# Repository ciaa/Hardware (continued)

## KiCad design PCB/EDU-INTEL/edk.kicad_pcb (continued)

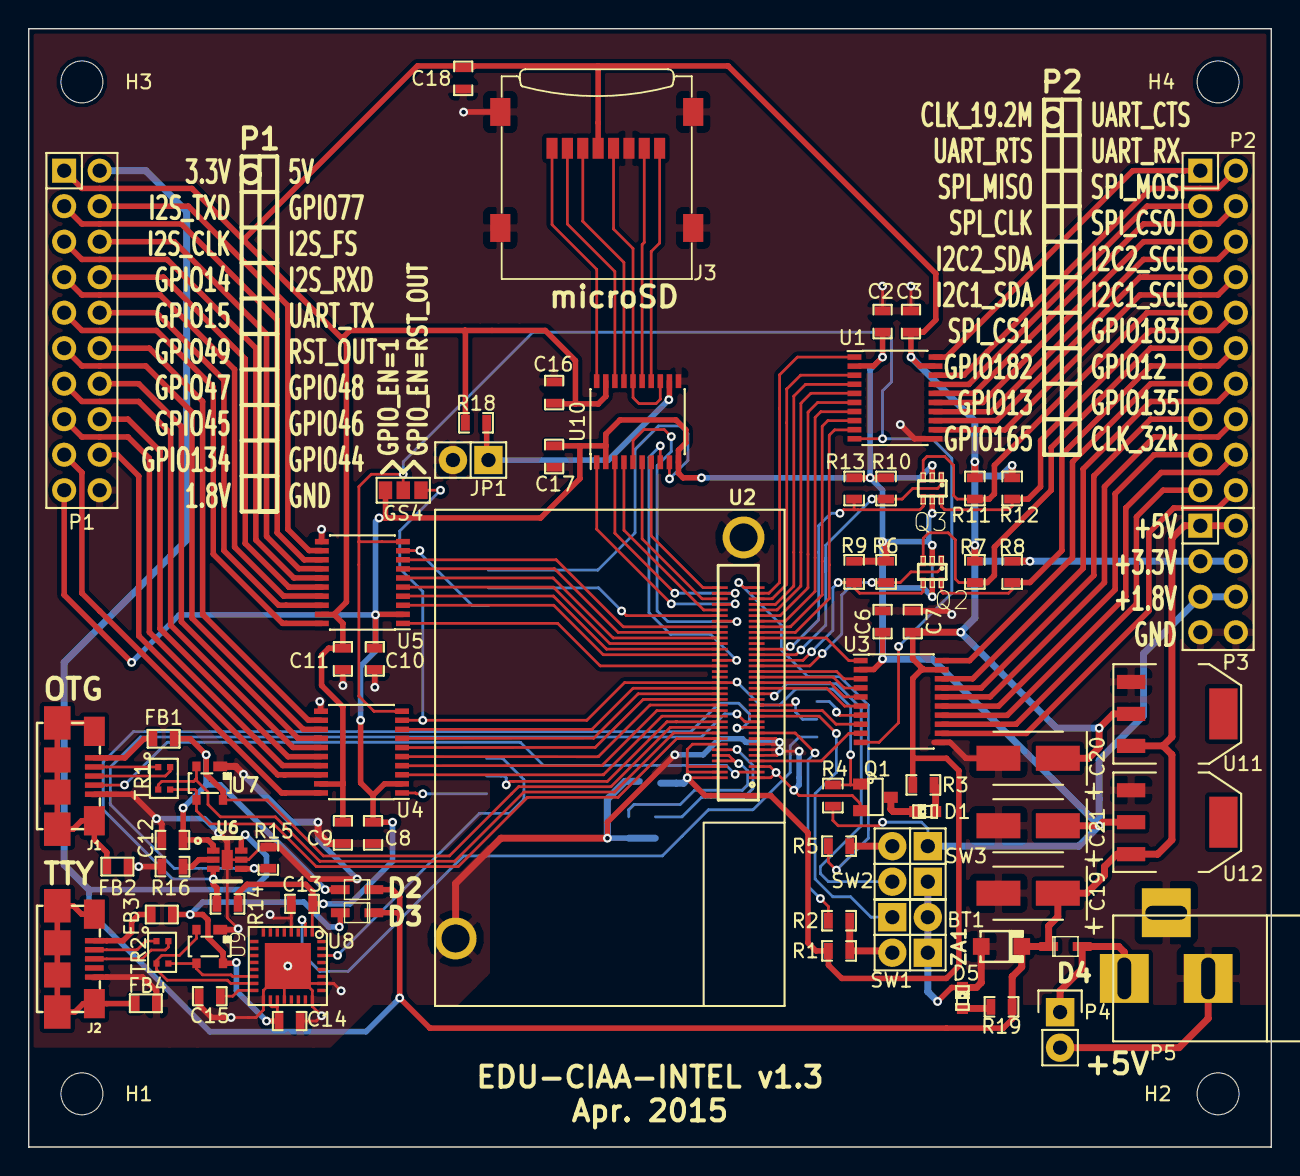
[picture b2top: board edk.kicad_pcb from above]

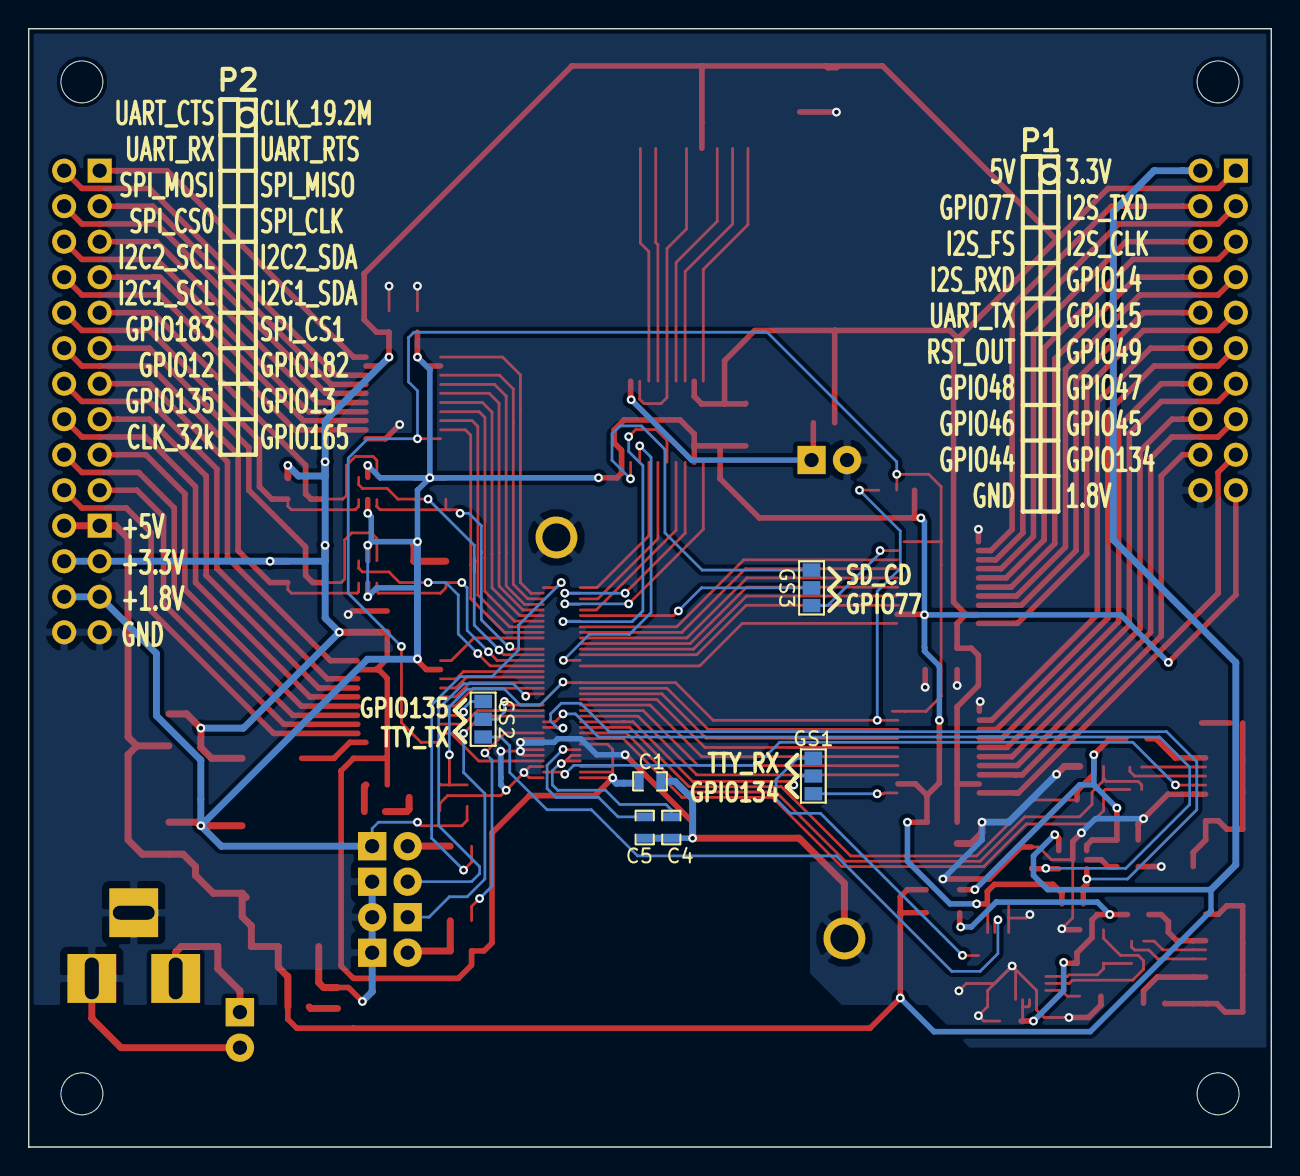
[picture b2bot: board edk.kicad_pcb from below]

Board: 2 copper layers, 88.9 x 80.0 mm, 87 parts (6 on the bottom side), 128 nets.

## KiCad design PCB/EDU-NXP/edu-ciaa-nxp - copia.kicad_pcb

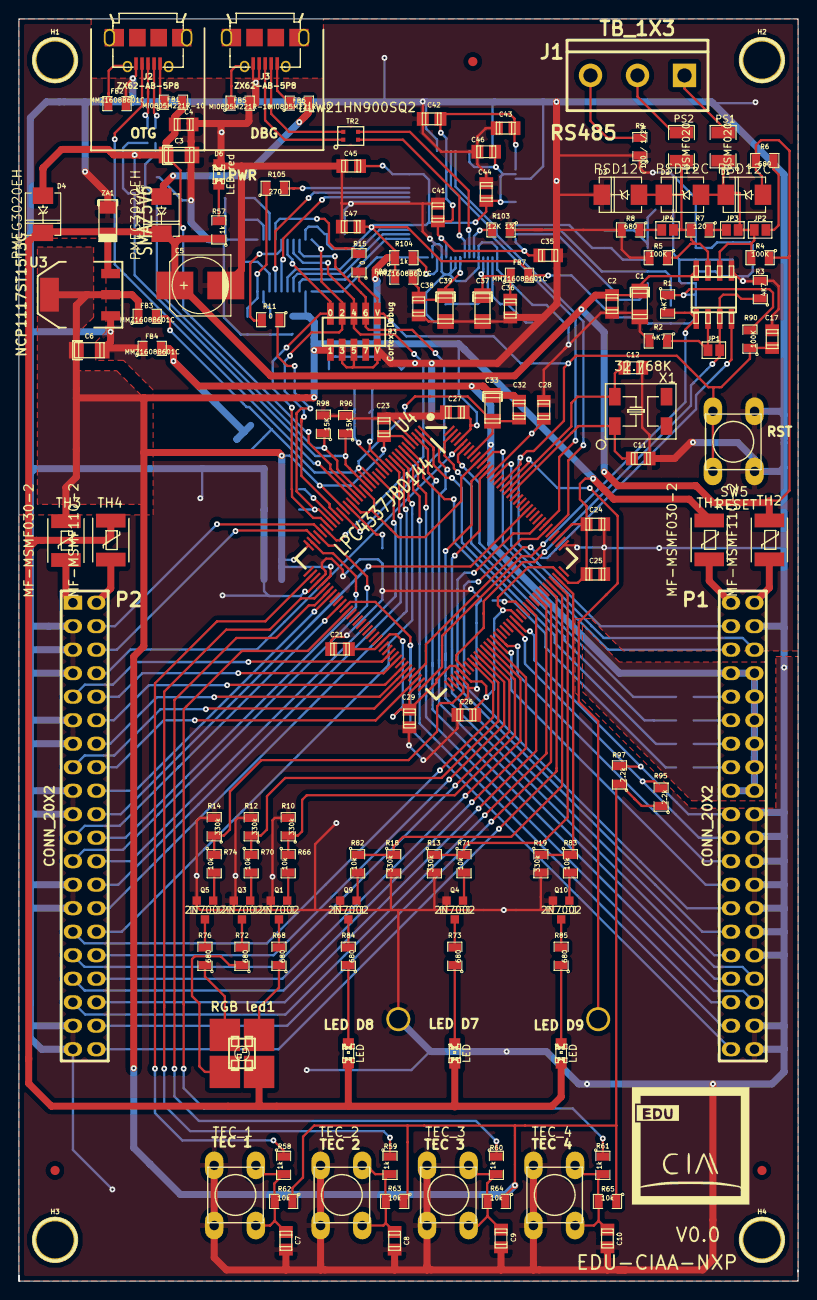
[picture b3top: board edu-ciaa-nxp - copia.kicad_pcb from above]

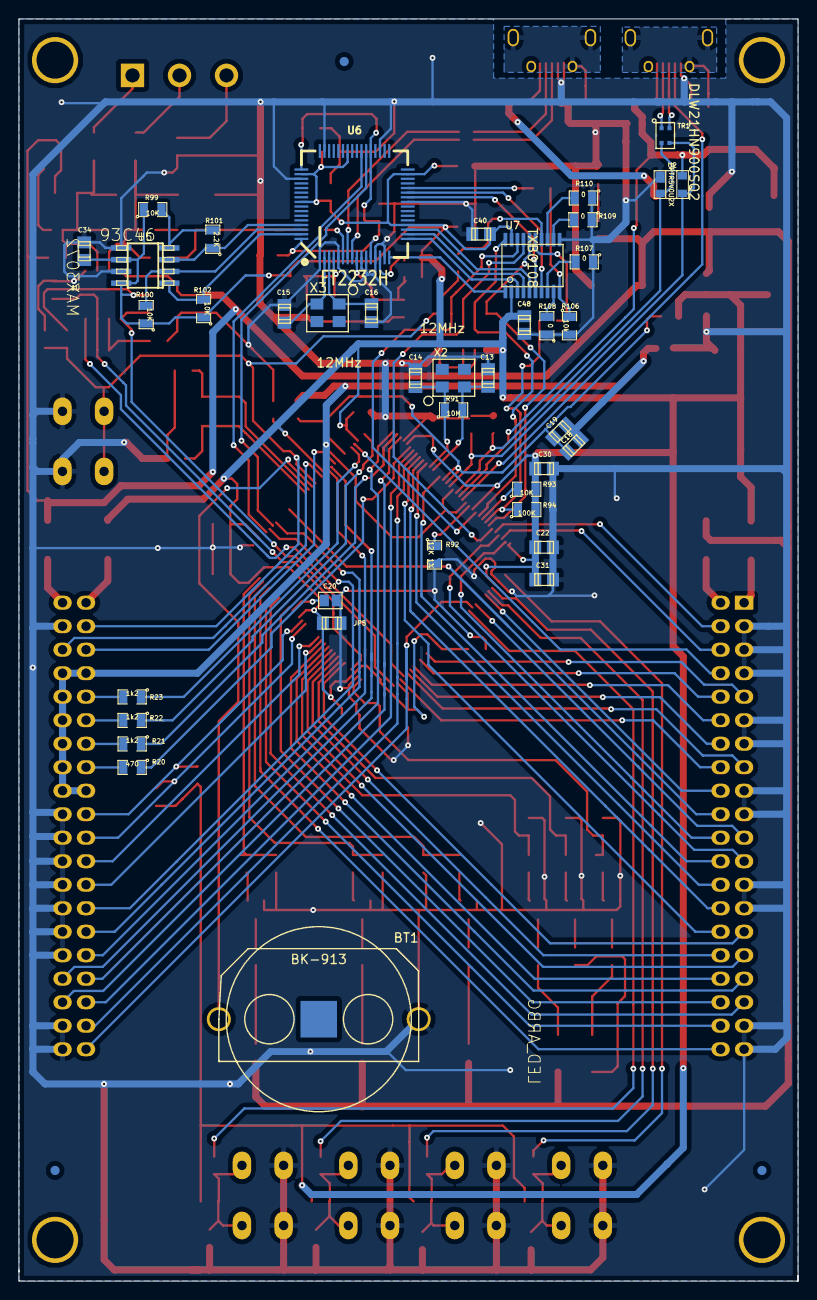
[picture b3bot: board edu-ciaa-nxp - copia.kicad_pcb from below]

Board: 2 copper layers, 84.2 x 136.4 mm, 181 parts (39 on the bottom side), 160 nets.

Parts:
BT1: BK-913; BK-913-ND
C1: 10uF / 6V3; c_1206_tantalio
C2, C4, C7, C8, C9, C10, C17, C18, C19, C20, C21, C22, C23, C24, C25, C26, C27, C28, C29, C30, C31, C32, C34, C36, C38, C40, C41, C42, C43, C44, C45, C46, C47, C48: 100nF; c_0805
C3, C6, C33, C37, C39: 10uF; c_1206_tantalio_1
C5: 330uF; c_elec_6.3x7.7
C11, C12: 15p; c_0805
C13, C14: 20p; c_0805
C15, C16: 22p; c_0805
C35: 3.3uF; c_0805
D1, D2, D3: PSD12C; DO-214AA(SMB)
D4, D5: PMEG3020EH; DO-214AA(SMB)
D6: LED red; LED-0805
D7, D8, D9: LED; LED-0805
F1, F2, F3: fiducial; Fiducial_1mm_TOP
F4, F5, F6: fiducial; Fiducial_1mm_BOT
FB1, FB5, FB6: MI0805M221R-10; SM0805
FB2, FB3, FB4, FB7, FB8: MMZ1608B601C; SM0805
H1, H2, H3, H4: 4mm; 1pin
J1: TB_1X3; bornier3
J2, J3: ZX62-AB-5P8; USB_microAB_ZX62-AB-5P8
JP1, JP2, JP3, JP4: JUMPER-2; GS2
JP5: ISP; GS2
LED1: LED_ARBG; PLCC-4
P1, P2: CONN_20X2; PIN_ARRAY_20X2
P3: Cortex-Debug; Pin_Array_5x2_1.27mm_SMD
PS1, PS2: USMF020; SM1210
Q1, Q3, Q4, Q5, Q9, Q10: 2N7002; SOT23GDS
R1, R2, R3: 4K7; SM0805
R4, R5, R90, R94: 100K; SM0805
R6, R8, R68, R72, R73, R76, R84, R85: 680; SM0805
R7: 120; SM0805
R9: 100 / 1/2W; SM0805
R10, R12, R13, R14, R18, R19: 330k; SM0805
R11, R15, R107, R108, R109, R110: 0; SM0805
R20: 470; SM0805
R21, R22, R23: 1k2; SM0805
R57, R58, R59, R60, R61, R104: 1k; SM0805
R62, R63, R64, R65, R66, R70, R71, R74, R82, R83, R106: 10k; SM0805
R91: 10M; SM0805
R92, R103: 12K 1%; SM0805
R93, R99, R100, R102: 10K; SM0805
R95, R97: 2.2k; SM0805
R96, R98: 15K; SM0805
R101: 2.2K; SM0805
R105: 270; SM0805
SW1: TEC_1; PUSH_SWITCH_THT
SW2: TEC_2; PUSH_SWITCH_THT
SW3: TEC_3; PUSH_SWITCH_THT
SW4: TEC_4; PUSH_SWITCH_THT
SW5: RESET; PUSH_SWITCH_THT
TH1, TH3: MF-MSMF030-2; MF-MSMF
TH2, TH4: MF-MSMF110-2; MF-MSMF
TR1, TR2: DLW21HN900SQ2; SRF2012
U1: MAX3072; -SOIC8
U2: PRTR5V0U2X; sot143B
U3: NCP1117ST15T3G; SOT223
U4: LPC4337JBD144; LQFP144-M05
U5: 93C46; -SOIC8
U6: FT2232H; LQFP64-M05
U7: TXB0108; tssop-20
X1: 32.768K; 4SOJ
X2, X3: 12MHz; FA238V-XTAL
ZA1: SMAZ5V6; SOD123F

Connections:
+3.3V: C6.1, C20.2, C21.2, C22.2, C23.2, C24.2, C25.2, C26.2, C27.2, C28.2, C29.2, C30.2, C31.2, C34.1, C40.2, C44.1, C45.1, C46.1, C47.1, C48.2, FB3.1, FB7.2, FB8.2, P3.1, R1.1, R62.1, R63.1, R64.1, R65.1, R90.2, R93.2, R94.2, R95.1, R97.1, R99.1, R100.1, R102.1, R104.1, TH1.2, TH3.2, U3.2, U3.4, U4.5, U4.25, U4.36, U4.41, U4.59, U4.71, U4.77, U4.94, U4.107, U4.111, U4.131, U4.141, U5.6, U5.8, U6.20, U6.31, U6.42, U6.50, U6.56, U7.2, U7.19
+3.3VADC: C18.1, C19.1, C32.1, C33.2, FB3.2, U4.16, U4.17, U4.137
+5V: C1.2, C2.1, C5.1, D1.1, D4.2, D5.2, D7.1, D8.1, D9.1, LED1.4, R4.1, R6.1, R57.1, TH2.2, TH4.2, U1.8, U3.3, ZA1.1
/CPU/ADC0_1: R21.1, U4.2
/CPU/ADC0_2: R22.1, U4.143
/CPU/ADC0_3: R23.1, U4.139
/CPU/CAN_RD: P1.27, U4.114
/CPU/CAN_TD: P1.29, U4.116
/CPU/CHJ3: FB5.1, J3.7
/CPU/DAC: R20.1, U4.6
/CPU/EECLK: R100.2, U5.2, U6.62
/CPU/EECS: R102.2, U5.1, U6.63
/CPU/EEDATA: R101.1, U5.3, U6.61
/CPU/ENET_CRS_DV: P2.10, U4.64
/CPU/ENET_MDC: P2.8, U4.140
/CPU/ENET_MDIO: P2.12, U4.66
/CPU/ENET_REF_CLK: P2.15, U4.68
/CPU/ENET_RXD0: P2.9, U4.62
/CPU/ENET_RXD1: P2.4, U4.32
/CPU/ENET_TXD0: P2.14, U4.67
/CPU/ENET_TXD1: P2.16, U4.70
/CPU/ENET_TX_EN: P2.6, U4.34
/CPU/FT_OE: R105.2, U6.28
/CPU/FT_RST: U6.27, U7.7
/CPU/FT_TCK: U6.16, U7.1
/CPU/FT_TDI: U6.17, U7.3
/CPU/FT_TDO: U6.18, U7.4
/CPU/FT_TMS: U6.19, U7.5
/CPU/FT_TRST: U6.26, U7.6
/CPU/FT_XTIN: C15.2, U6.2, X3.2
/CPU/FT_XTOUT: C16.2, U6.3, X3.1
/CPU/GPIO0: P2.29, U4.80
/CPU/GPIO1: P2.32, U4.82
/CPU/GPIO2: P2.31, U4.83
/CPU/GPIO3: P2.34, U4.85
/CPU/GPIO4: P2.33, U4.86
/CPU/GPIO5: P2.36, U4.97
/CPU/GPIO6: P2.35, U4.100
/CPU/GPIO7: P2.38, U4.101
/CPU/GPIO8: P2.40, U4.103
/CPU/I2C_SCL: P1.21, R95.2, U4.92
/CPU/I2C_SDA: P1.19, R97.2, U4.93
/CPU/ISP: P1.5, U4.134
/CPU/LCD1: P2.30, U4.9
/CPU/LCD2: P2.28, U4.10
/CPU/LCD3: P2.26, U4.11
/CPU/LCD4: P2.22, U4.35
/CPU/LCD_RS: P2.24, U4.15
/CPU/LED0_B: R10.1, R66.1, U4.84
/CPU/LED0_G: R12.1, R70.1, U4.81
/CPU/LED0_R: R14.1, R74.1, U4.75
/CPU/LED1: R18.1, R82.1, U4.104
/CPU/LED2: R13.1, R71.1, U4.105
/CPU/LED3: R19.1, R83.1, U4.106
/CPU/PULS_0: R58.1, U4.38
/CPU/PULS_1: R59.1, U4.42
/CPU/PULS_2: R60.1, U4.43
/CPU/PULS_3: R61.1, U4.49
/CPU/RESET: C17.1, P1.3, P3.10, R15.1, R90.1, SW5.1, SW5.2, U4.128
/CPU/RS232_RXD: P1.23, U4.88
/CPU/RS232_TXD: P1.25, U4.87
/CPU/RS485_DIR: JP1.1, R3.1, U1.3, U4.78
/CPU/RS485_RXD: R1.2, U1.1, U4.72
/CPU/RS485_TXD: U1.4, U4.69
/CPU/RST: R15.2, U7.14
/CPU/RTCX1: C11.2, U4.125, X1.1
/CPU/RTCX2: C12.2, U4.126, X1.4
/CPU/SPI_MISO: P2.18, U4.44
/CPU/SPI_MOSI: P2.21, U4.47
/CPU/SPI_SCK: P2.20, U4.120
/CPU/TCK: P3.4, U4.27, U7.20
/CPU/TDI: P3.8, U4.26, U7.18
/CPU/TDO: P3.6, U4.31, U7.17
/CPU/TEC_COL0: P1.39, U4.48
/CPU/TEC_COL1: P1.31, U4.132
/CPU/TEC_COL2: P1.34, U4.133
/CPU/TEC_F0: P1.33, U4.1
/CPU/TEC_F1: P1.36, U4.3
/CPU/TEC_F2: P1.37, U4.8
/CPU/TEC_F3: P1.35, U4.7
/CPU/TMS: P3.2, U4.30, U7.16
/CPU/TRST: R11.2, U7.15
/CPU/U2_RXD: U4.115, U6.38
/CPU/U2_TXD: U4.113, U6.39
/CPU/USB_DEBUG_VBUS: D5.1, FB6.2
/CPU/USB_DM: R98.1, TR1.2, U2.2, U4.20
/CPU/USB_DP: R96.1, TR1.3, U2.3, U4.18
/CPU/USB_ID: J2.4, U4.22
/CPU/USB_JTAG_1.8V: C35.1, C41.1, C42.1, C43.1, U6.12, U6.37, U6.49, U6.64
/CPU/USB_JTAG_DM: TR2.3, U6.7
/CPU/USB_JTAG_DP: TR2.2, U6.8
/CPU/USB_VBUS: C3.1, C4.1, D4.1, FB1.2, U2.4, U4.21
/CPU/XTAL1: C14.2, R91.1, U4.12, X2.1
/CPU/XTAL2: C13.2, R91.2, U4.13, X2.2
/CPU/nTRST: R11.1, R94.1, U4.29
/GPIO/LCD_EN: P2.23, U4.33
/GPIO/WAKEUP: P1.6, U4.130
/USB OTG/CHJ2: FB2.2, J2.7
GND: BT1.2, C1.1, C2.2, C3.2, C4.2, C5.2, C6.2, C7.2, C8.2, C9.2, C10.2, C11.1, C12.1, C13.1, C14.1, C15.1, C16.1, C17.2, C20.1, C21.1, C22.1, C23.1, C24.1, C25.1, C26.1, C27.1, C28.1, C29.1, C30.1, C31.1, C34.2, C35.2, C36.2, C37.2, C38.2, C39.2, C40.1, C41.2, C42.2, C43.2, C44.2, C45.2, C46.2, C47.2, C48.1, D3.2, D6.2, FB2.1, FB4.1, FB5.2, J2.5, J3.4, J3.5, JP5.1, P1.4, P1.20, P1.22, P1.24, P1.26, P1.28, P1.30, P1.32, P1.38, P1.40, P2.3, P2.5, P2.7, P2.11, P2.13, P2.17, P2.19, P2.25, P2.27, P2.37, P2.39, P3.3, P3.5, P3.9, Q1.S, Q3.S, Q4.S, Q5.S, Q9.S, Q10.S, R2.2, R3.2, R5.2, R8.2, R9.1, R10.2, R12.2, R13.2, R14.2, R18.2, R19.2, R92.2, R96.2, R98.2, R103.1, R106.2, R107.1, R108.1, R109.1, R110.1, SW1.3, SW1.4, SW2.3, SW2.4, SW3.3, SW3.4, SW4.3, SW4.4, SW5.3, SW5.4, U1.5, U2.1, U3.1, U4.4, U4.40, U4.76, U4.109, U5.5, U5.7, U6.1, U6.5, U6.10, U6.11, U6.13, U6.15, U6.25, U6.35, U6.47, U6.51, U7.11, ZA1.2
GNDA: C18.2, C19.2, C32.2, C33.1, FB4.2, P1.7, P1.8, P1.10, P1.12, P1.14, P1.16, P1.17, P1.18, U4.19, U4.23, U4.135
unnamed: R110.2, U7.13
unnamed: R109.2, U7.12
unnamed: C36.1, C37.1, FB7.1, U6.4
unnamed: C38.1, C39.1, FB8.1, U6.9
unnamed: FB6.1, J3.1
unnamed: J3.2, TR2.4
unnamed: R103.2, U6.6
unnamed: R104.2, U6.14
unnamed: BT1.1, U4.127
unnamed: R93.1, U4.28
unnamed: JP5.2, U4.96
unnamed: R92.1, U4.24
unnamed: R107.2, U7.8
unnamed: R108.2, U7.9
unnamed: R105.1, R106.1, U7.10
unnamed: R99.2, R101.2, U5.4
unnamed: J3.3, TR2.1
unnamed: J1.2, PS2.2
unnamed: J1.3, R9.2
unnamed: D1.2, D2.1, JP2.1, JP3.2, PS1.1, R4.2, U1.6
unnamed: JP4.1, R8.1
unnamed: JP2.2, R6.2
unnamed: JP3.1, R7.1
unnamed: J1.1, PS1.2
unnamed: JP1.2, R2.1, U1.2
unnamed: D2.2, D3.1, JP4.2, PS2.1, R5.1, R7.2, U1.7
unnamed: D6.1, R57.2
unnamed: J2.2, TR1.1
unnamed: J2.3, TR1.4
unnamed: FB1.1, J2.1
unnamed: P2.1, TH3.1
unnamed: P2.2, TH4.1
unnamed: P1.2, TH2.1
unnamed: P1.9, R23.2
unnamed: P1.11, R22.2
unnamed: P1.13, R21.2
unnamed: P1.15, R20.2
unnamed: P1.1, TH1.1
unnamed: Q5.G, R74.2
unnamed: Q5.D, R76.2
unnamed: Q3.G, R70.2
unnamed: LED1.3, R72.1
unnamed: Q3.D, R72.2
unnamed: Q10.D, R85.2
unnamed: D9.2, R85.1
unnamed: Q10.G, R83.2
unnamed: D7.2, R73.1
unnamed: Q4.G, R71.2
unnamed: Q4.D, R73.2
unnamed: LED1.2, R76.1
unnamed: C9.1, R60.2, R64.2, SW3.1, SW3.2
unnamed: Q9.G, R82.2
unnamed: D8.2, R84.1
unnamed: Q9.D, R84.2
unnamed: Q1.D, R68.2
unnamed: Q1.G, R66.2
unnamed: LED1.1, R68.1
unnamed: C10.1, R61.2, R65.2, SW4.1, SW4.2
unnamed: C7.1, R58.2, R62.2, SW1.1, SW1.2
unnamed: C8.1, R59.2, R63.2, SW2.1, SW2.2

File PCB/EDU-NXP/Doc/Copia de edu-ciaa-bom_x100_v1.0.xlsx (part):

Componente | Cantidad por PCB | Referencia | Descripción | Código Digi-Key | Código Mouser | Cantidad para 100 PCBs | Costo unitario x100 (USD FOB DigiKey) | Costo por PCB x100 (USD FOB DigiKey) | Costo unitario x1000(USD FOB DigiKey) | Costo por PCB x1000 (USD FOB DigiKey)
BK-913 | 1 | BT1 | Soporte batería CR2032 | BK-913-ND | 534-3003 | 100 | 0.27 | 0.27 | 2.1999999999999999E-2 | 2.1999999999999999E-2
15pF | 2 | C11 C12 | Cap. Cerámico 0805 | 1276-1163-1-ND | 581-08055A150J | 200 | 2.1999999999999999E-2 | 4.3999999999999997E-2 | 1.2E-2 | 2.4E-2
20pF | 2 | C13 C14 | Cap. Cerámico 0805 | 399-8033-1-ND | 81-GQM2195C1H200JB01 | 200 | 0.1008 | 0.2016 | 6.1199999999999997E-2 | 0.12239999999999999
22pF | 2 | C15 C16 | Cap. Cerámico 0805 | 399-1113-1-ND | 80-C0805C220J5G | 200 | 2.24E-2 | 4.48E-2 | 1.2E-2 | 2.4E-2
100nF | 34 | C2 C4 C7 C8 C9 C10 C17 C18 C19 C20 C21 C22 C23 C24 C25 C26 C27 C28 C29 C30 C31 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 | Cap. Cerámico 0805 | 399-1167-1-ND | 581-08055C104J | 3400 | 3.56E-2 | 1.2103999999999999 | 2.0629999999999999E-2 | 0.70141999999999993
3.3uF | 1 | C35 | Cap. Cerámico 0805 | 445-7582-1-ND | 810-C2012X5R1H335K | 100 | 0.16070000000000001 | 0.16070000000000001 | 0.10349999999999999 | 0.10349999999999999
10uF | 6 | C1 C3 C6 C33 C37 C39 | Cap. Cerámico 1206 | 399-3525-1-ND | 81-GRM31CR71C106KAC7 | 600 | 0.17499999999999999 | 1.0499999999999998 | 0.115 | 0.69000000000000006
330uF | 1 | C5 | Cap. Aluminio SMD | 493-9422-1-ND | 647-UCW1E331MNL1GS | 100 | 0.40610000000000002 | 0.40610000000000002 | 0.34060000000000001 | 0.34060000000000001
PSD12C | 3 | D1 D2 D3 | TVS | P6SMB12CAT3GOSCT-ND | 863-P6SMB12CAT3G | 300 | 0.28770000000000001 | 0.86309999999999998 | 0.14745 | 0.44235000000000002
PMEG3020EH | 2 | D4 D5 | Diodo Schottky | 568-4129-1-ND | 771-PMEG3020EH-T/R | 200 | 0.2505 | 0.501 | 0.12839 | 0.25678000000000001
LED | 4 | D6 D7 D8 D9 | LED Rojo 0805 | 1080-1412-1-ND | 78-VLMS1300-GS08 | 400 | 0.2112 | 0.8448 | 0.1152 | 0.46079999999999999
BLM18KG221SN1 | 3 | FB1 FB5 FB6 | EMI Filter 0603 | 490-5255-1-ND | 81-BLM18KG221SN1D | 300 | 5.2299999999999999E-2 | 0.15689999999999998 | 3.0099999999999998E-2 | 9.0299999999999991E-2
HZ0805E601R-10 | 5 | FB2 FB3 FB4 FB7 FB8 | EMI Filter 0805 | 240-2399-1-ND | 875-HZ0805E601R-10 | 500 | 3.8100000000000002E-2 | 0.1905 | 2.1950000000000001E-2 | 0.10975
TB_1X3 | 1 | J1 | Bornes fijos x3 | ED2610-ND | 571-7969493 | 100 | 0.36799999999999999 | 0.36799999999999999 | 0.26400000000000001 | 0.26400000000000001
ZX62-AB-5PA | 2 | J2 J3 | Conector micro USB tipo AB | H11635CT-ND | 798-ZX62-AB-5PA11 | 200 | 0.77439999999999998 | 1.5488 | 0.56320000000000003 | 1.1264000000000001
LED RGB | 1 | LED1 | led RGB SDM | 160-2022-1-ND | 859-LTST-C19FD1WT | 100 | 0.29930000000000001 | 0.29930000000000001 | 0.17100000000000001 | 0.17100000000000001
Pines 2x20 | 2 | P1 P2 | Tira de pines 2x20 | S6104-ND |  | 200 | 1.6938 | 3.3875999999999999 | 1.25153 | 2.5030600000000001
Conector IDE | 1 | P3 | Conector 2x5 1.27mm SMD para DEBUG | 952-1389-ND | 855-M50-3600542 | 100 | 0.88 | 0.88 | 0.64 | 0.64
USMF020 | 2 | PS1 PS2 | Polyswitch | MF-USMF020-2CT-ND | 652-MF-USMF020-2 | 200 | 0.22639999999999999 | 0.45279999999999998 |  | 0
2N7002 | 12 | Q1 Q2 Q3 Q4 Q5 Q6 Q7 Q8 Q9 Q10 Q11 Q12 | Mosfet canal N SOT23 | 2N7002NCT-ND | 512-2N7002 | 1200 | 0.1363 | 1.6356000000000002 | 4.5420000000000002E-2 | 0.54503999999999997
0 | 4 | R107 R108 R109 R110 | Resistor SMD 0805 | 311-0.0ARCT-ND | 667-ERJ-6GEY0R00V | 400 | 7.3000000000000001E-3 | 2.92E-2 | 3.2599999999999999E-3 | 1.304E-2
4K7 | 3 | R1 R2 R3 | Resistor SMD 0805 | 1276-5544-1-ND | 667-ERJ-S06J472V | 300 | 7.1000000000000004E-3 | 2.1299999999999999E-2 | 3.2100000000000002E-3 | 9.6299999999999997E-3
100K | 2 | R4 R5 | Resistor SMD 0805 | RR12P100KDCT-ND | 667-ERJ-6GEYJ104V | 200 | 1.49E-2 | 2.98E-2 | 5.4400000000000004E-3 | 1.0880000000000001E-2
680 | 8 | R6 R8 R68 R72 R73 R76 R84 R85 | Resistor SMD 0805 | RR12P680DCT-ND | 754-RR1220P-681D | 800 | 7.3000000000000001E-3 | 5.8400000000000001E-2 | 3.2599999999999999E-3 | 2.6079999999999999E-2
120 | 1 | R7 | Resistor SMD 0805 | RR12P120DCT-ND | 667-ERJ-6GEYJ121V | 100 | 1.49E-2 | 1.49E-2 | 5.4400000000000004E-3 | 5.4400000000000004E-3
100 1/2W | 1 | R9 | Resistor SMD 0805 1/2W | P16057CT-ND | 667-ERJ-P06J101V | 100 | 6.6500000000000004E-2 | 6.6500000000000004E-2 | 2.4320000000000001E-2 | 2.4320000000000001E-2
330K | 6 | R10 R11 R12 R13 R14 R15 R16 R17 R18 R19 | Resistor SMD 0805 | RMCF0805JT330KCT-ND | 667-ERJ-6GEYJ334V | 600 | 8.8000000000000005E-3 | 5.28E-2 | 3.2000000000000002E-3 | 1.9200000000000002E-2
470 | 1 | R20 | Resistor SMD 0806 | P470ACT-ND | 603-AC0805JR-07470RL | 100 | 1.49E-2 | 1.49E-2 | 5.4000000000000003E-3 | 5.4000000000000003E-3
1K2 | 3 | R21 R22 R23 | Resistor SMD 0807 | RMCF0805JT1K20CT-ND | 660-RK73B2ATTD122J | 300 | 8.8000000000000005E-3 | 2.64E-2 | 3.2000000000000002E-3 | 9.6000000000000009E-3
1K | 6 | R57 R58 R59 R60 R61 R104 | Resistor SMD 0805 | 311-1.0KARCT-ND | 667-ERJ-6GEYJ102V | 600 | 7.3000000000000001E-3 | 4.3799999999999999E-2 | 3.2599999999999999E-3 | 1.9560000000000001E-2
10K | 17 | R62 R63 R64 R65 R66 R70 R71 R74 R82 R83 R90 R93 R94 R99 R100 R102 R106 | Resistor SMD 0805 | P10KACT-ND | 667-ERJ-6GEYJ103V | 1700 | 1.49E-2 | 0.25330000000000003 | 5.4400000000000004E-3 | 9.2480000000000007E-2
10M | 1 | R91 | Resistor SMD 0805 | RMCF0805JT10M0CT-ND | 667-ERJ-6GEYJ106V | 100 | 8.8000000000000005E-3 | 8.8000000000000005E-3 | 3.2000000000000002E-3 | 3.2000000000000002E-3
12K | 1 | R92 R103 | Resistor SMD 0805 1% | 311-12.0KCRCT-ND | 667-ERJ-S06F1202V | 100 | 8.3999999999999995E-3 | 8.3999999999999995E-3 | 3.79E-3 | 3.79E-3
2K2 | 3 | R95 R97 R101 | Resistor SMD 0805 | RMCF0805JT2K20CT-ND | 660-RK73B2ATTDD222J | 300 | 8.8000000000000005E-3 | 2.64E-2 | 3.2000000000000002E-3 | 9.6000000000000009E-3
15K | 2 | R96 R98 | Resistor SMD 0805 | RR12P15.0KDCT-ND | 754-RR1220P-153D | 200 | 3.8100000000000002E-2 | 7.6200000000000004E-2 | 1.6729999999999998E-2 | 3.3459999999999997E-2
270 | 1 | R105 | Resistor SMD 0805 | RHM270CPCT-ND | 660-RK73B2ATTDD271J | 100 | 1.04E-2 | 1.04E-2 | 4.6600000000000001E-3 | 4.6600000000000001E-3
PULSADOR | 5 | TEC_1 TEC_2 TEC_3 RESET | Tact switch SPST | 450-1792-1-ND | 612-TL3301BF260QG | 500 | 0.21540000000000001 | 1.077 | 0.1943 | 0.97150000000000003
MF-MSMF030-2 | 1 | TH1 TH3 | Polyswitch 0.3A SMD | MF-MSMF030-2CT-ND | 652-MF-MSMF030-2 | 100 | 0.24260000000000001 | 0.24260000000000001 | 0.18690000000000001 | 0.18690000000000001
MF-MSMF110-2 | 2 | TH2 TH4 | Polyswitch 1.1A SMD | MF-USMF110-2CT-ND | 652-MF-MSMF110-2 | 200 | 0.22639999999999999 | 0.45279999999999998 | 0.15920000000000001 | 0.31840000000000002
DLW21HN900SQ2 | 2 | TR1 TR2 | Choke USB | SRF2012-900YCT-ND | 81-DLW21HN900SQ2L | 200 | 0.33600000000000002 | 0.67200000000000004 | 0.24640000000000001 | 0.49280000000000002
SN65HVD1176DR | 1 | U1 | Transceptor RS485 SOIC8 | 296-26337-1-ND | 595-SN65HVD1176DR | 100 | 3.1017000000000001 | 3.1017000000000001 | 2.1168 | 2.1168
PRTR5V0U2X | 1 | U2 | TVS para USB SOT143 | 568-4140-1-ND | 771-PRTR5V0U2X-T/R | 100 | 0.35780000000000001 | 0.35780000000000001 | 0.20265 | 0.20265
NCP1117ST33T3G | 1 | U3 | Regulador 3.3V SOT223 | NCP1117ST33T3GOSCT-ND | 863-NCP1117ST33T3G | 100 | 0.31269999999999998 | 0.31269999999999998 | 0.17710000000000001 | 0.17710000000000001
LPC4337JBD144 | 1 | U4 | Microcontrolador LQFP144 | 568-10159-ND | 771-LPC4337JBD144E | 100 | 11.05 | 11.05 | 8.6449999999999996 | 8.6449999999999996
93C46 | 1 | U5 | EEPROM SOIC8 | AT93C46DN-SH-TCT-ND | 579-93C46A-E/SN | 100 | 0.22950000000000001 | 0.22950000000000001 | 0.21708 | 0.21708
FT2232H | 1 | U6 | USB IC 64-LQFP | 768-1024-1-ND | 895-FT2232HL | 100 | 5.4 | 5.4 | 4.0599999999999996 | 4.0599999999999996
TXB0108 | 1 | U7 | Buffer bidireccional 20-TSSOP | 296-21527-1-ND | 595-TXB0108PWR | 100 | 1.6704000000000001 | 1.6704000000000001 | 0.9 | 0.9
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
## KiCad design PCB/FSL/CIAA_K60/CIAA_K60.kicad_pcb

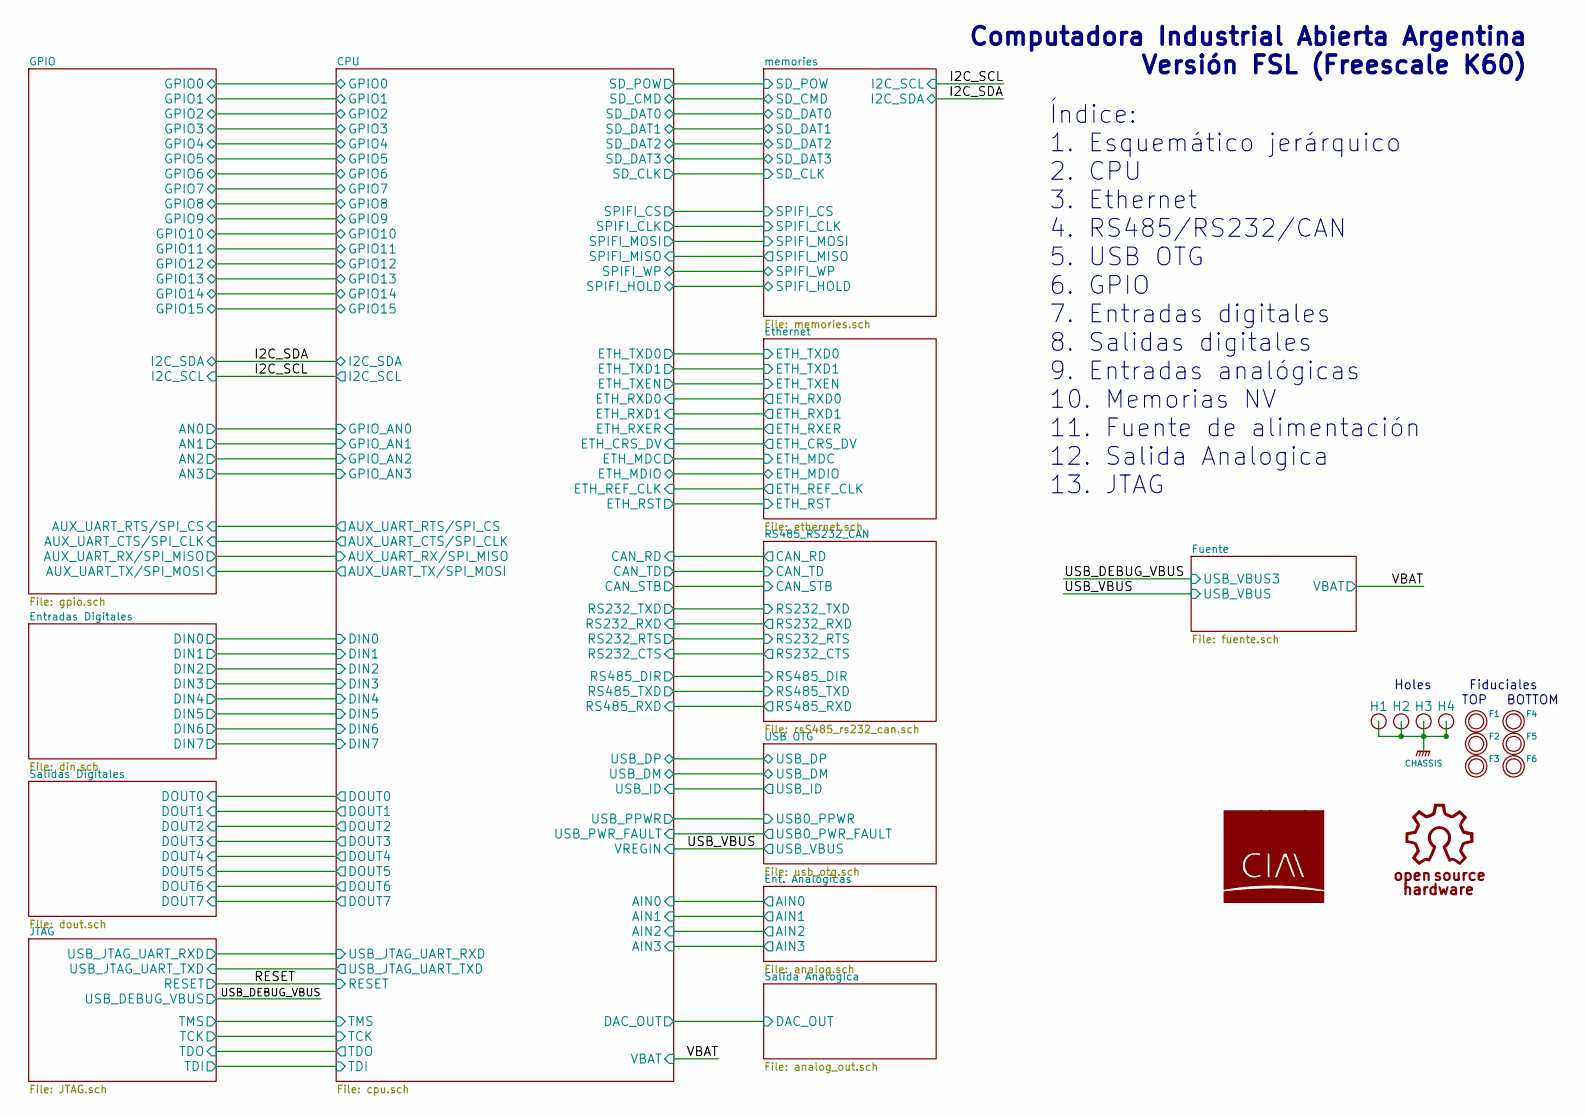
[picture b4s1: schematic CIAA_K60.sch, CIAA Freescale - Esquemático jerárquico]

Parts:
F1, F2, F3, F4, F5, F6: FIDUCIAL; Fiducial_1mm
G101: OSHWA
G102: LOGO_CIAA; LOGO-CIAA
H1, H2, H3, H4: PCB_HOLE

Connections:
GNDPWR: H1.1, H2.1, H3.1, H4.1; also elsewhere on the board

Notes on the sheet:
Índice: 1. Esquemático jerárquico 2. CPU 3. Ethernet 4. RS485/RS232/CAN 5. USB OTG 6. GPIO 7. Entradas digitales 8. Salidas digitales 9. Entradas analógicas 10. Memorias NV 11. Fuente de alimentación 12. Salida Analogica 13. JTAG
Computadora Industrial Abierta Argentina Versión FSL (Freescale K60)
Fiduciales
TOP
BOTTOM
Holes
